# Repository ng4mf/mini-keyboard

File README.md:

# mini-keyboard
Intro Eagle circuit design project that will involve putting together a PCB that can play notes.

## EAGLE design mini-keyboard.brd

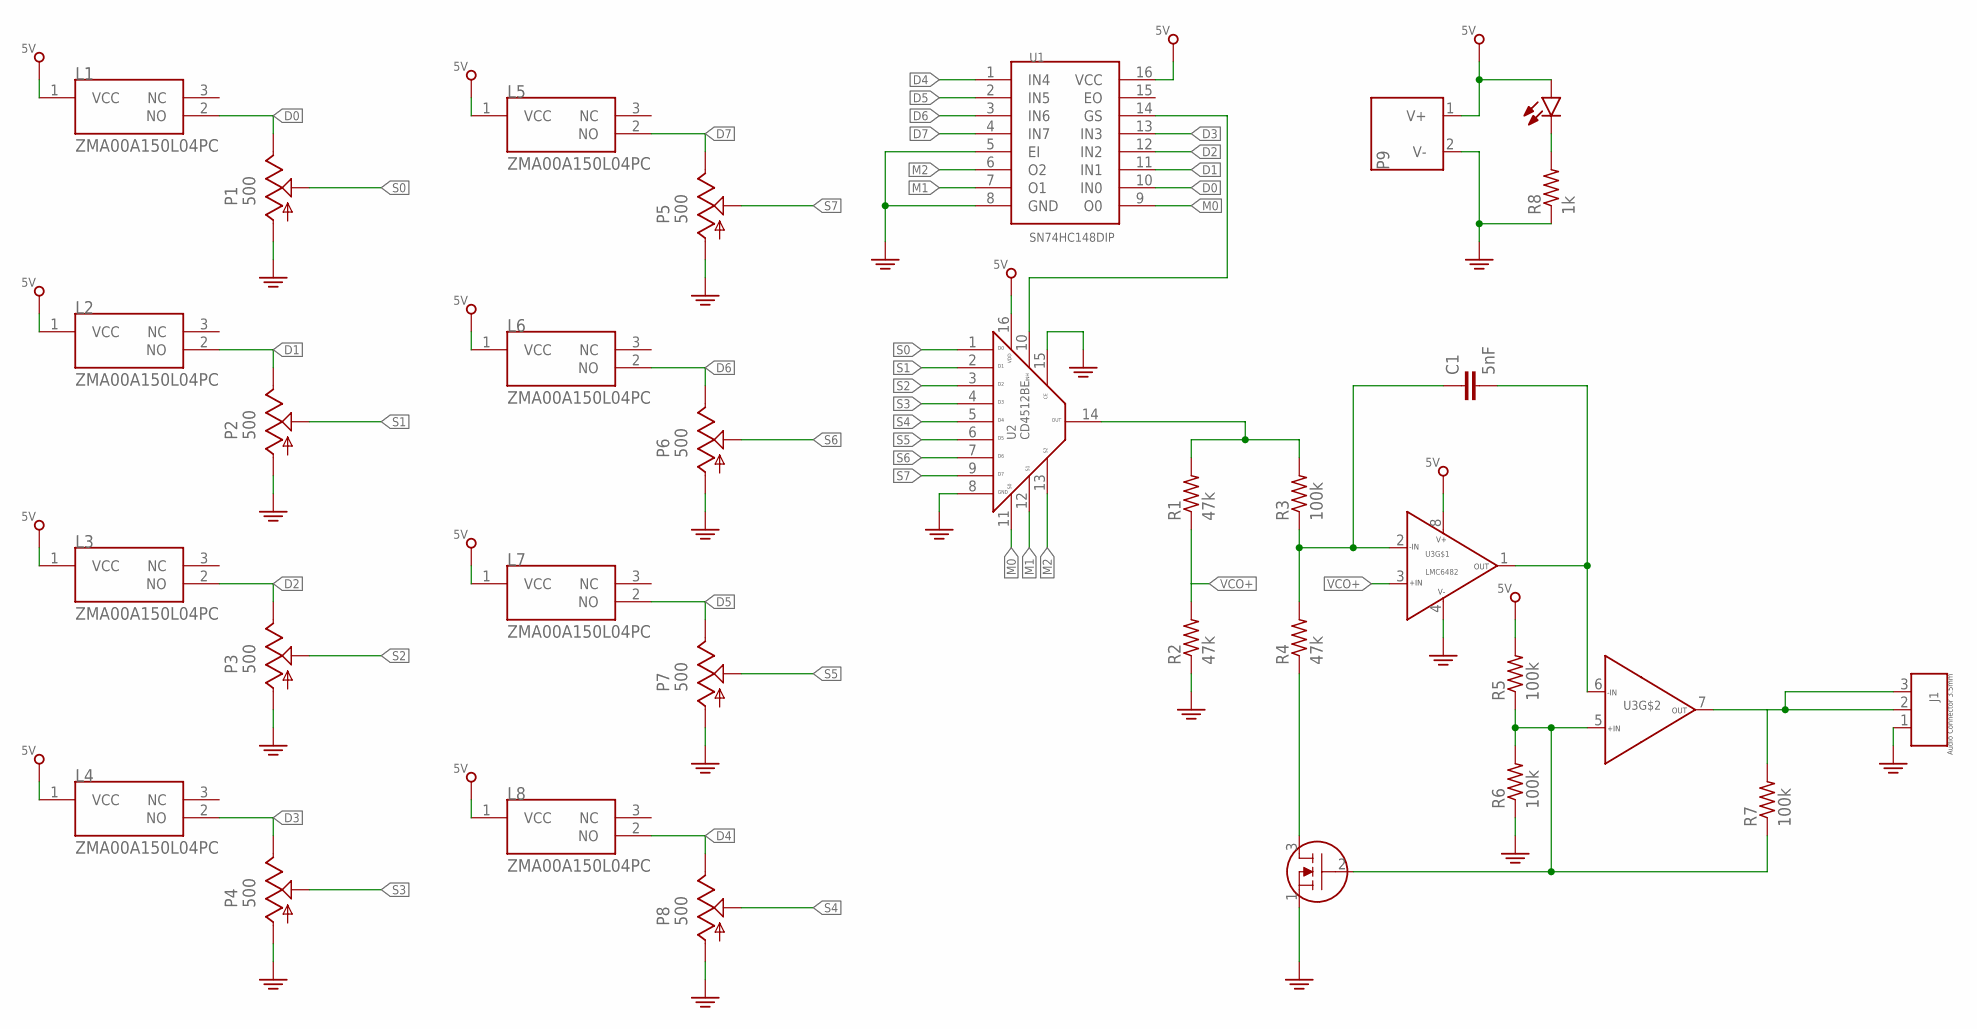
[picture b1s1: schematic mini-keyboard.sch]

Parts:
C1: 5nF; 0603
J1: SJ-3523-SMT; SJ-352X-SMT
L1, L2, L3, L4, L5, L6, L7, L8: ZMA00A150L04PC; ZMA-LIMSWITCH
P1, P2, P3, P4, P5, P6, P7, P8: 500; 3214X
P9: SINGLE-LINE; BARREL-SPFUN-BRBRD
PWR: LED-STD; 0603
R1, R2, R4: 47k; 0603
R3, R5, R6, R7: 100k; 0603
R8: 1k; 0603
U1: SN74HC148DIP; PDIP-16
U2: CD4512BE; PDIP-16
U3: LMC6482; DIL08
U23: 2N7000-G; TO92-CBE

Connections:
5V: L1.1 (VCC), L2.1 (VCC), L3.1 (VCC), L4.1 (VCC), L5.1 (VCC), L6.1 (VCC), L7.1 (VCC), L8.1 (VCC), P9.1 (V+), PWR.IN, R5.2, U1.16 (VCC), U2.16 (VDD), U3.8 (VCC)
D0: L1.2 (NO), P1.3 (E), U1.10 (IN0)
D1: L2.2 (NO), P2.3 (E), U1.11 (IN1)
D2: L3.2 (NO), P3.3 (E), U1.12 (IN2)
D3: L4.2 (NO), P4.3 (E), U1.13 (IN3)
D4: L8.2 (NO), P8.3 (E), U1.1 (IN4)
D5: L7.2 (NO), P7.3 (E), U1.2 (IN5)
D6: L6.2 (NO), P6.3 (E), U1.3 (IN6)
D7: L5.2 (NO), P5.3 (E), U1.4 (IN7)
GND: J1.1, P1.1 (A), P2.1 (A), P3.1 (A), P4.1 (A), P5.1 (A), P6.1 (A), P7.1 (A), P8.1 (A), P9.2 (V-), R2.1, R6.1, R8.1, U1.5 (EI), U1.8 (GND), U2.8 (GND), U2.15 (DISABLE), U3.4 (GND), U23.1 (S)
M0: U1.9 (O0), U2.11 (S0)
M1: U1.7 (O1), U2.12 (S1)
M2: U1.6 (O2), U2.13 (S2)
unnamed: R4.1, U23.3 (D)
unnamed: R1.2, R3.2, U2.14 (OUT)
unnamed: U1.14 (GS), U2.10 (INHIBIT)
unnamed: C1.1, R3.1, R4.2, U3.2 (-INA)
unnamed: J1.2, J1.3, R7.2, U3.7 (OUTB)
unnamed: R5.1, R6.2, R7.1, U3.5 (+INB), U23.2 (G)
unnamed: PWR.OUT, R8.2
unnamed: C1.2, U3.1 (OUTA), U3.6 (-INB)
S0: P1.2 (S), U2.1 (D0)
S1: P2.2 (S), U2.2 (D1)
S2: P3.2 (S), U2.3 (D2)
S3: P4.2 (S), U2.4 (D3)
S4: P8.2 (S), U2.5 (D4)
S5: P7.2 (S), U2.6 (D5)
S6: P6.2 (S), U2.7 (D6)
S7: P5.2 (S), U2.9 (D7)
VCO+: R1.1, R2.2, U3.3 (+INA)

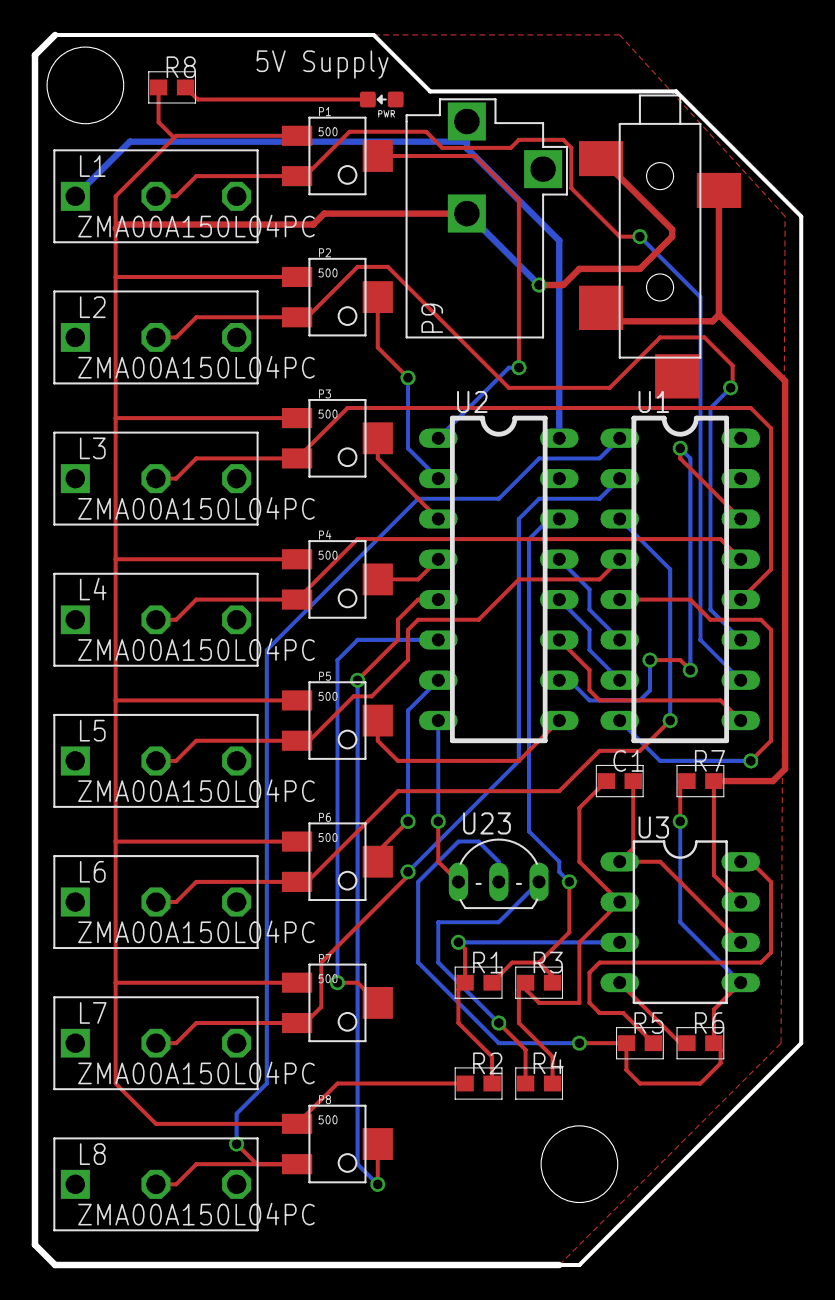
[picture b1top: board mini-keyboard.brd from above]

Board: 2 copper layers, 48.2 x 77.5 mm, 32 parts (0 on the bottom side), 30 nets.

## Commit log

2016-10-14 First version, no power conn or output conn
2016-10-20 Finished board, added pwr connector, LED, and audio connector for 3.5mm stereo
